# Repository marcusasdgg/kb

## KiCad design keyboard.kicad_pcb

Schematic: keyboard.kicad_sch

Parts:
D1: BLE indicator
D2: Capslock indicator
D_0, D_1, D_2, D_3, D_4, D_5, D_6, D_7, D_8, D_9, D_10, D_11, D_12, D_13, D_14, D_15, D_16, D_17, D_18, D_19, D_20, D_21, D_22, D_23, D_24, D_25, D_26, D_27, D_28, D_29, D_30, D_31, D_32, D_33, D_34, D_35, D_36, D_37, D_38, D_39, D_40, D_41, D_42, D_43, D_44, D_45, D_46, D_47, D_48, D_49, D_50, D_51, D_52, D_53, D_54, D_55, D_56, D_57, D_58, D_59, D_60, D_61, D_62, D_63, D_64, D_65, D_66, D_67, D_68, D_69, D_70, D_71, D_72, D_73, D_74, D_75, D_76, D_77, D_78, D_79, D_80, D_81, D_82, D_83, D_84, D_85, D_86: D; D_SOD-123
H1: D-
H2: D+
H3: OUT+
H4: OUT-
K_0, K_1, K_2, K_3, K_4, K_5, K_6, K_7, K_8, K_9, K_10, K_11, K_12, K_13, K_14, K_15, K_16, K_17, K_18, K_19, K_20, K_21, K_22, K_23, K_24, K_25, K_26, K_27, K_28, K_30, K_31, K_32, K_34, K_35, K_36, K_37, K_38, K_39, K_40, K_41, K_42, K_43, K_44, K_45, K_47, K_48, K_49, K_51, K_52, K_53, K_54, K_55, K_56, K_57, K_58, K_59, K_60, K_61, K_64, K_65, K_66, K_67, K_68, K_69, K_70, K_71, K_72, K_73, K_75, K_84, K_85, K_86: KEYSW; MX-1U-NoLED
K_29: KEYSW; MX-2U-NoLED
K_33, K_46: KEYSW; MX-1.5U-NoLED
K_50: KEYSW; MX-1.75U-NoLED
K_62, K_63: KEYSW; MX-2.25U-NoLED
K_74: KEYSW; MX-2.75U-NoLED
K_76, K_77, K_78, K_80, K_81, K_82, K_83: KEYSW; MX-1.25U-NoLED
K_79: KEYSW; MX-6.25U-NoLED
R1, R2: R
SW1: RotaryEncoder; RotaryEncoder_Bourns_Horizontal_PEC09-2xxxF-Nxxxx

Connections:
unnamed: D1.2 (A), R1.1
unnamed: D2.2 (A), R2.1
col0: K_0.1, K_16.1, K_33.1, K_50.1, K_76.1
col1: K_17.1, K_63.1, K_77.1
col2: K_1.1, K_18.1, K_34.1, K_51.1, K_64.1
col3: K_2.1, K_19.1, K_35.1, K_52.1, K_65.1, K_78.1
col4: K_3.1, K_20.1, K_36.1, K_53.1, K_66.1
col5: K_4.1, K_21.1, K_37.1, K_54.1, K_67.1
col6: K_22.1, K_38.1, K_55.1, K_68.1, K_79.1
col7: K_5.1, K_23.1, K_39.1, K_56.1, K_69.1
col8: K_6.1, K_24.1, K_40.1, K_57.1, K_70.1
col9: K_7.1, K_25.1, K_41.1, K_58.1, K_71.1
col10: K_8.1, K_26.1, K_42.1, K_59.1, K_72.1, K_80.1
col11: K_9.1, K_27.1, K_43.1, K_60.1, K_73.1, K_81.1
col12: K_10.1, K_28.1, K_44.1, K_61.1
col13: K_11.1, K_45.1, K_62.1, K_74.1, K_82.1
col14: K_12.1, K_29.1, K_46.1, K_83.1
col15: K_13.1, K_30.1, K_47.1, K_84.1
col16: K_14.1, K_31.1, K_48.1, K_75.1, K_85.1
col17: K_15.1, K_32.1, K_49.1, K_86.1
row0: D_0.1 (K_1), D_1.1 (K_1), D_2.1 (K_1), D_3.1 (K_1), D_4.1 (K_1), D_5.1 (K_1), D_6.1 (K_1), D_7.1 (K_1), D_8.1 (K_1), D_9.1 (K_1), D_10.1 (K_1), D_11.1 (K_1), D_12.1 (K_1), D_13.1 (K_1), D_14.1 (K_1), D_15.1 (K_1)
row2: D_16.1 (K_1), D_17.1 (K_1), D_18.1 (K_1), D_19.1 (K_1), D_20.1 (K_1), D_21.1 (K_1), D_22.1 (K_1), D_23.1 (K_1), D_24.1 (K_1), D_25.1 (K_1), D_26.1 (K_1), D_27.1 (K_1), D_28.1 (K_1), D_29.1 (K_1), D_30.1 (K_1), D_31.1 (K_1), D_32.1 (K_1)
row3: D_33.1 (K_1), D_34.1 (K_1), D_35.1 (K_1), D_36.1 (K_1), D_37.1 (K_1), D_38.1 (K_1), D_39.1 (K_1), D_40.1 (K_1), D_41.1 (K_1), D_42.1 (K_1), D_43.1 (K_1), D_44.1 (K_1), D_45.1 (K_1), D_46.1 (K_1), D_47.1 (K_1), D_48.1 (K_1), D_49.1 (K_1)
row4: D_50.1 (K_1), D_51.1 (K_1), D_52.1 (K_1), D_53.1 (K_1), D_54.1 (K_1), D_55.1 (K_1), D_56.1 (K_1), D_57.1 (K_1), D_58.1 (K_1), D_59.1 (K_1), D_60.1 (K_1), D_61.1 (K_1), D_62.1 (K_1)
row5: D_63.1 (K_1), D_64.1 (K_1), D_65.1 (K_1), D_66.1 (K_1), D_67.1 (K_1), D_68.1 (K_1), D_69.1 (K_1), D_70.1 (K_1), D_71.1 (K_1), D_72.1 (K_1), D_73.1 (K_1), D_74.1 (K_1), D_75.1 (K_1)
row6: D_76.1 (K_1), D_77.1 (K_1), D_78.1 (K_1), D_79.1 (K_1), D_80.1 (K_1), D_81.1 (K_1), D_82.1 (K_1), D_83.1 (K_1), D_84.1 (K_1), D_85.1 (K_1), D_86.1 (K_1)

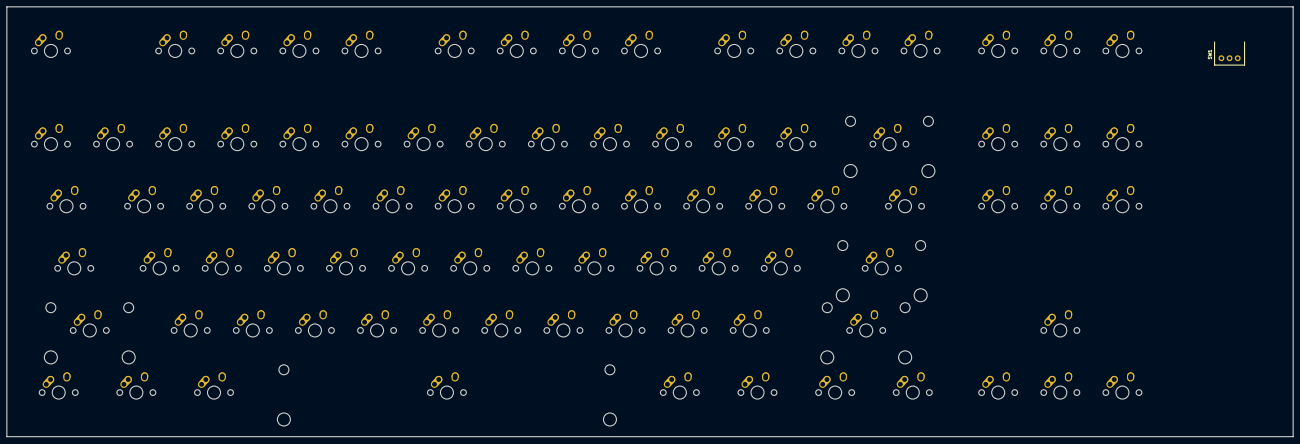
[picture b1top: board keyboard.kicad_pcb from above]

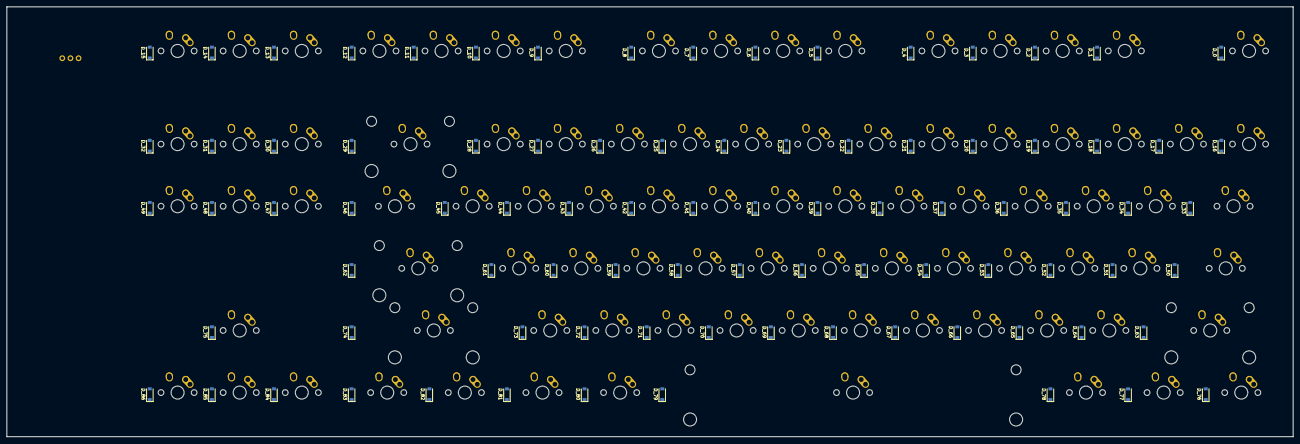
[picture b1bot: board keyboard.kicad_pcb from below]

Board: 2 copper layers, 394.5 x 131.8 mm, 175 parts (87 on the bottom side), 24 nets, no tracks yet.
